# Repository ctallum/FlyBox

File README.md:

# FlyBox - Olin Brandeis Rosbash Lab HMMI FlyBox Redesign SCOPE Project

# About the Firmware
All the source code and documentation for the FlyBox firmware can be found [here](https://github.com/ctallum/FlyBox-firmware)

# About the Web UI
All the source code and documentation for the webside can be found [here](https://github.com/ctallum/FlyBox/tree/main/programming-gui)

## Test Creator Website
To access the website, visit:
https://rosbash-lab-flybox.github.io/FlyBox/

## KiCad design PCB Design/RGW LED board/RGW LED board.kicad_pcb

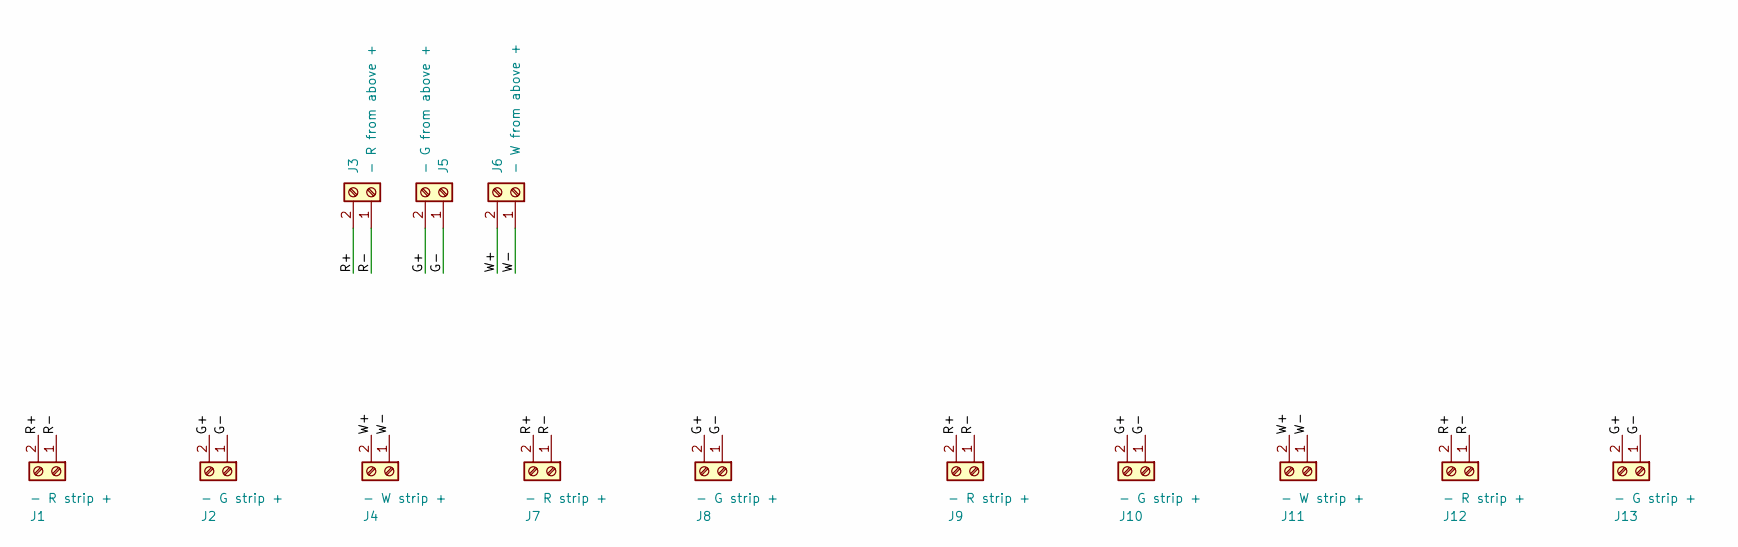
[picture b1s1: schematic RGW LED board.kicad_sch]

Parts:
J1, J7, J9, J12: - R strip +; TerminalBlock_bornier-2_P5.08mm
J2, J8, J10, J13: - G strip +; TerminalBlock_bornier-2_P5.08mm
J3: - R from above +; TerminalBlock_bornier-2_P5.08mm
J4, J11: - W strip +; TerminalBlock_bornier-2_P5.08mm
J5: - G from above +; TerminalBlock_bornier-2_P5.08mm
J6: - W from above +; TerminalBlock_bornier-2_P5.08mm

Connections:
/G+: J2.2, J5.2, J8.2, J10.2, J13.2
/G-: J2.1, J5.1, J8.1, J10.1, J13.1
/R+: J1.2, J3.2, J7.2, J9.2, J12.2
/R-: J1.1, J3.1, J7.1, J9.1, J12.1
/W+: J4.2, J6.2, J11.2
/W-: J4.1, J6.1, J11.1

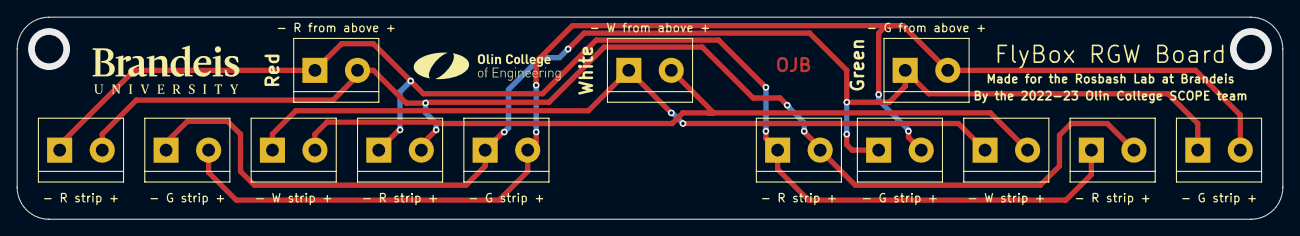
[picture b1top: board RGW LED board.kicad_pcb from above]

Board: 2 copper layers, 151.1 x 24.1 mm, 13 parts (0 on the bottom side), 6 nets.

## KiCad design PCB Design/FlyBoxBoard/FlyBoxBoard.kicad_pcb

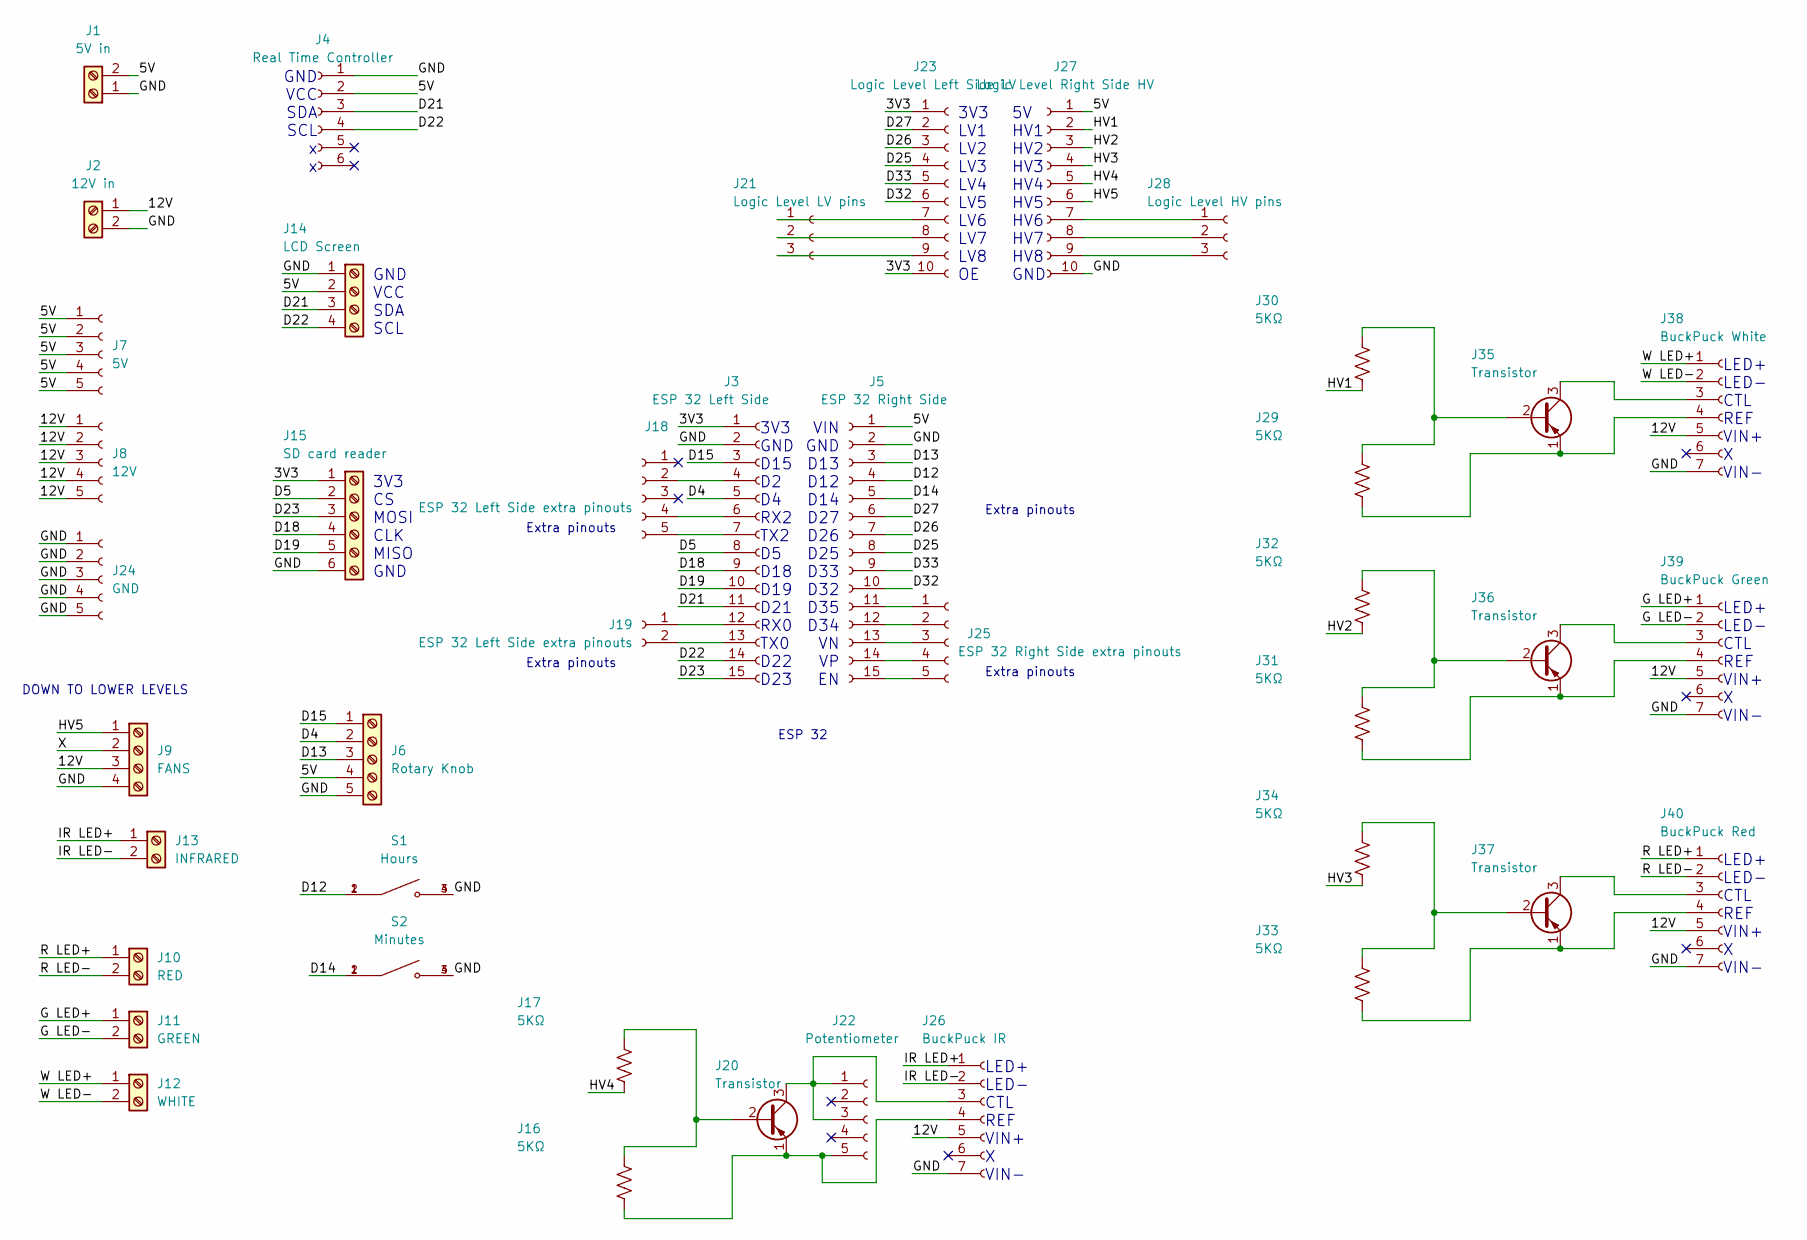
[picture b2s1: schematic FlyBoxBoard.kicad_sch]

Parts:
J1: 5V in; TerminalBlock_bornier-2_P5.08mm
J2: 12V in; TerminalBlock_bornier-2_P5.08mm
J3: ESP 32 Left Side; PinSocket_1x15_P2.54mm_Vertical
J4: Real Time Controller; PinSocket_1x06_P2.54mm_Vertical
J5: ESP 32 Right Side; PinSocket_1x15_P2.54mm_Vertical
J6: Rotary Knob; TerminalBlock_bornier-5_P5.08mm
J7: 5V; PinSocket_1x05_P2.54mm_Vertical
J8: 12V; PinSocket_1x05_P2.54mm_Vertical
J9: FANS; TerminalBlock_bornier-4_P5.08mm
J10: RED; TerminalBlock_bornier-2_P5.08mm
J11: GREEN; TerminalBlock_bornier-2_P5.08mm
J12: WHITE; TerminalBlock_bornier-2_P5.08mm
J13: INFRARED; TerminalBlock_bornier-2_P5.08mm
J14: LCD Screen; TerminalBlock_bornier-4_P5.08mm
J15: SD card reader; TerminalBlock_bornier-6_P5.08mm
J16, J17, J29, J30, J31, J32, J33, J34: 5KΩ; R_0805_2012Metric_Pad1.20x1.40mm_HandSolder
J18: ESP 32 Left Side extra pinouts; PinSocket_1x05_P2.54mm_Vertical
J19: ESP 32 Left Side extra pinouts; PinSocket_1x02_P2.54mm_Vertical
J20, J35, J36, J37: Transistor; TO-92_Inline
J21: Logic Level LV pins; PinSocket_1x03_P2.54mm_Vertical
J22: Potentiometer; PinSocket_1x05_P2.54mm_Vertical
J23: Logic Level Left Side LV; PinSocket_1x10_P2.54mm_Vertical
J24: GND; PinSocket_1x05_P2.54mm_Vertical
J25: ESP 32 Right Side extra pinouts; PinSocket_1x05_P2.54mm_Vertical
J26: BuckPuck IR; PinSocket_1x07_P2.54mm_Vertical
J27: Logic Level Right Side HV; PinSocket_1x10_P2.54mm_Vertical
J28: Logic Level HV pins; PinSocket_1x03_P2.54mm_Vertical
J38: BuckPuck White; PinSocket_1x07_P2.54mm_Vertical
J39: BuckPuck Green; PinSocket_1x07_P2.54mm_Vertical
J40: BuckPuck Red; PinSocket_1x07_P2.54mm_Vertical
S1: Hours; SW_1571563-2; PARTREV V
S2: Minutes; SW_1571563-2; PARTREV V

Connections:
/3V3: J3.1, J15.1, J23.1, J23.10
/5V: J1.2, J4.2, J5.1, J6.4, J7.1, J7.2, J7.3, J7.4, J7.5, J14.2, J27.1
/12V: J2.1, J8.1, J8.2, J8.3, J8.4, J8.5, J9.3, J26.5, J38.5, J39.5, J40.5
/D4: J3.5, J6.2
/D5: J3.8, J15.2
/D12: J5.4, S1.1, S1.2
/D13: J5.3, J6.3
/D14: J5.5, S2.1, S2.2
/D15: J3.3, J6.1
/D18: J3.9, J15.4
/D19: J3.10, J15.5
/D21: J3.11, J4.3, J14.3
/D22: J3.14, J4.4, J14.4
/D23: J3.15, J15.3
/D25: J5.8, J23.4
/D26: J5.7, J23.3
/D27: J5.6, J23.2
/D32: J5.10, J23.6
/D33: J5.9, J23.5
/G LED+: J11.1, J39.1
/G LED-: J11.2, J39.2
/GND: J1.1, J2.2, J3.2, J4.1, J5.2, J6.5, J9.4, J14.1, J15.6, J24.1, J24.2, J24.3, J24.4, J24.5, J26.7, J27.10, J38.7, J39.7, J40.7, S1.3, S1.4, S2.3, S2.4
/HV1: J27.2, J30.2
/HV2: J27.3, J32.2
/HV3: J27.4, J34.2
/HV4: J17.2, J27.5
/HV5: J9.1, J27.6
/IR LED+: J13.1, J26.1
/IR LED-: J13.2, J26.2
/R LED+: J10.1, J40.1
/R LED-: J10.2, J40.2
/W LED+: J12.1, J38.1
/W LED-: J12.2, J38.2
/X: J9.2
unnamed: J16.1, J17.1, J20.2 (B)
unnamed 35: J16.2, J20.1 (E), J22.5, J26.4; also elsewhere on the board
unnamed: J3.4, J18.2
unnamed: J3.6, J18.4
unnamed: J3.7, J18.5
unnamed: J3.12, J19.1
unnamed: J3.13, J19.2
unnamed 41: J20.3 (C), J22.1, J22.3, J26.3; also elsewhere on the board
unnamed: J21.1, J23.7
unnamed: J21.2, J23.8
unnamed: J21.3, J23.9
unnamed: J5.11, J25.1
unnamed: J5.12, J25.2
unnamed: J5.13, J25.3
unnamed: J5.14, J25.4
unnamed: J5.15, J25.5
unnamed: J27.7, J28.1
unnamed: J27.8, J28.2
unnamed: J27.9, J28.3
unnamed: J29.1, J30.1, J35.2 (B)
unnamed: J29.2, J35.1 (E), J38.4
unnamed: J31.1, J32.1, J36.2 (B)
unnamed: J31.2, J36.1 (E), J39.4
unnamed: J33.1, J34.1, J37.2 (B)
unnamed: J33.2, J37.1 (E), J40.4
unnamed: J35.3 (C), J38.3
unnamed: J36.3 (C), J39.3
unnamed: J37.3 (C), J40.3

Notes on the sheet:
3V3 CS MOSI CLK MISO GND
DOWN TO LOWER LEVELS
VIN GND D13 D12 D14 D27 D26 D25 D33 D32 D35 D34 VN VP EN
GND VCC SDA SCL
3V3 LV1 LV2 LV3 LV4 LV5 LV6 LV7 LV8 OE
5V HV1 HV2 HV3 HV4 HV5 HV6 HV7 HV8 GND
ESP 32
3V3 GND D15 D2 D4 RX2 TX2 D5 D18 D19 D21 RX0 TX0 D22 D23
Extra pinouts
LED+ LED- CTL REF VIN+ X VIN-
GND VCC SDA SCL x x

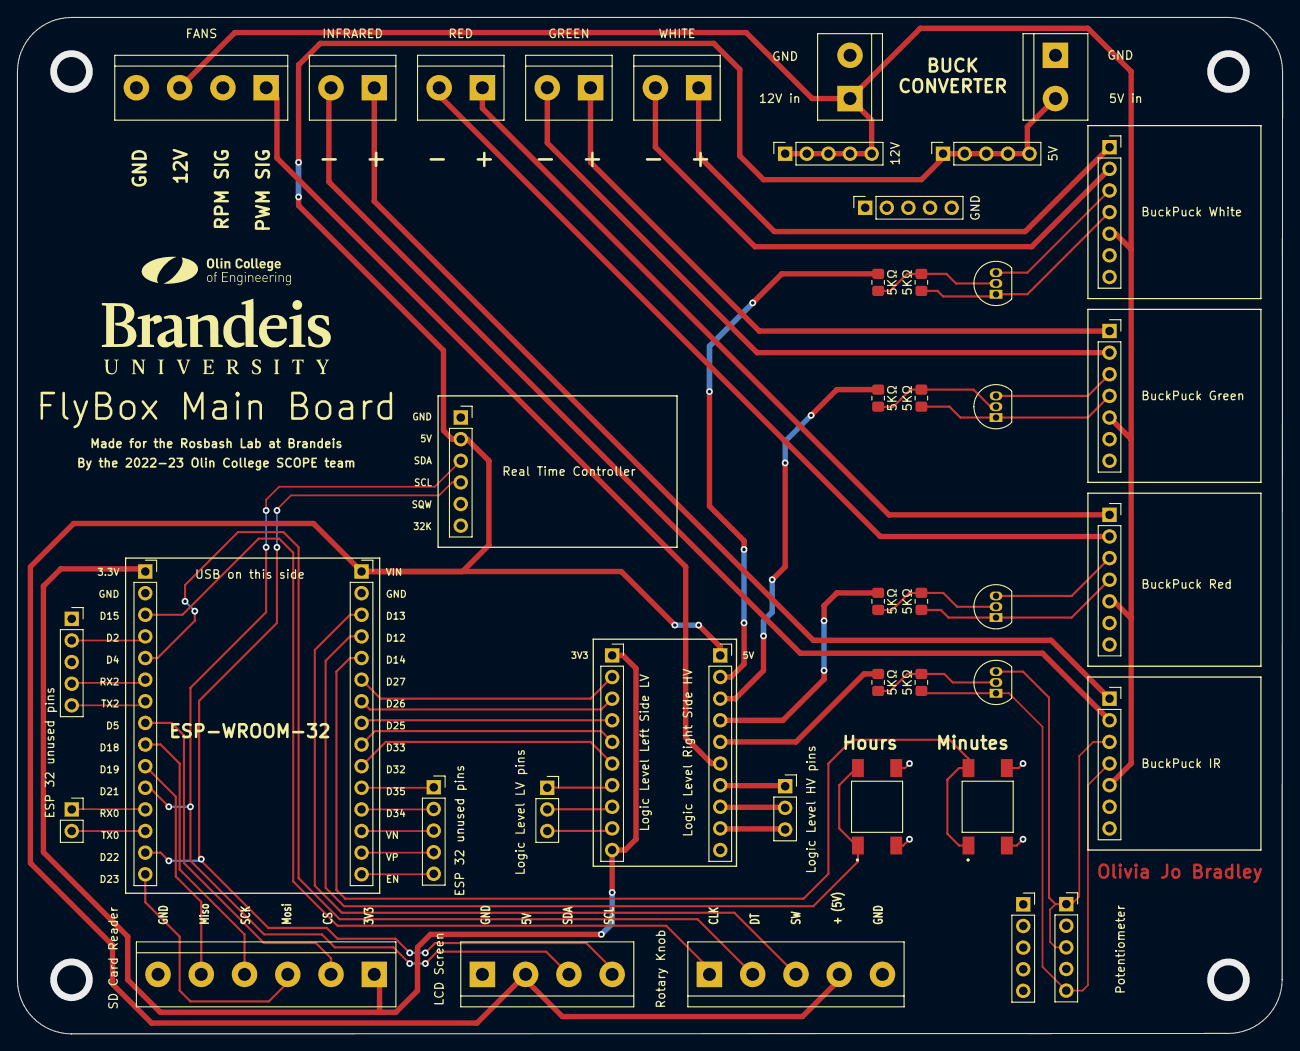
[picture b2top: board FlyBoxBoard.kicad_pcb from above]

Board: 2 copper layers, 148.6 x 119.4 mm, 43 parts (0 on the bottom side), 61 nets.

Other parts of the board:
J22#2: Potentiometer; PinSocket_1x05_P2.54mm_Vertical

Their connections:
unnamed 35: J22#2.5; also elsewhere on the board
unnamed 41: J22#2.1, J22#2.3; also elsewhere on the board

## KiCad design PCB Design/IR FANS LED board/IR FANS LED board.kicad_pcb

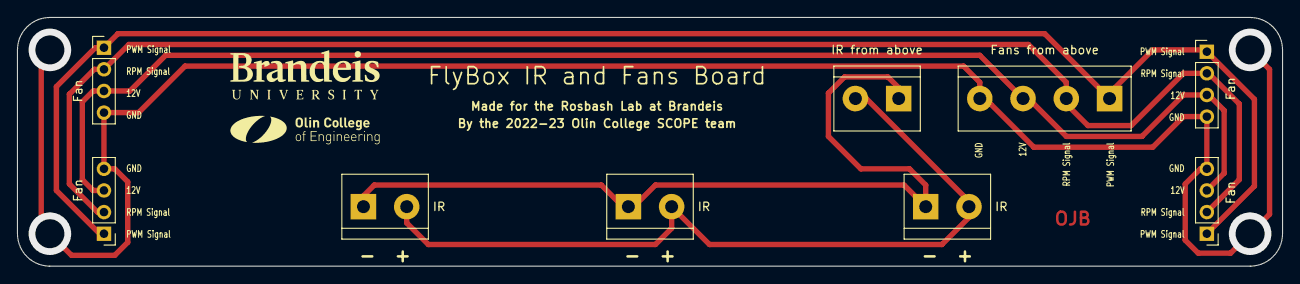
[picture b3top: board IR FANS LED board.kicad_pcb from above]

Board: 2 copper layers, 148.6 x 29.2 mm, 9 parts (0 on the bottom side), 6 nets.

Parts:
J1, J2, J8, J9: Fan; PinHeader_1x04_P2.54mm_Vertical
J3, J5, J7: IR; TerminalBlock_bornier-2_P5.08mm
J4: Fans from above; TerminalBlock_bornier-4_P5.08mm
J6: IR from above; TerminalBlock_bornier-2_P5.08mm

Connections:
/12V: J1.3, J2.3, J4.3, J8.3, J9.3
/GND: J1.4, J2.4, J4.4, J8.4, J9.4
/HV5: J1.1, J2.1, J4.1, J8.1, J9.1
/IR LED+: J3.2, J5.2, J6.2, J7.2
/IR LED-: J3.1, J5.1, J6.1, J7.1
/X: J1.2, J2.2, J4.2, J8.2, J9.2

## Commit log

2022-10-12 Add sample flybox Arduino code
2022-10-12 Add test copy of RedLED example code to experiment with
2022-11-16 V1
    Front end mostly done, back end not started
2022-11-16 Add Arduino code and profile.json
2022-11-16 clean up repo
2022-11-16 Fix typo in profile.txt file
2022-11-17 Download working
    Downloading items sort of works, but uses a new button that's not in the header. I'm going to try to fix this in further versions.
2022-11-17 Download fully working
    Download button is now in the right spot. Refresh button works but upload does not.
2022-11-30 Uploading LED test code + Temp sensor
2022-12-01 Item colors working properly
    About to try implementing upload button, but things are working for the moment.
2022-12-07 Upload button working
    Upload button works, item drag precision increased to one minute, clicking on timeline creates new event.
2022-12-07 Update firmware to deserialize by chunk and create file selection menu
2022-12-09 Updated with ESP Pins
    #define WHITEPIN 26
    #define REDPIN 25
    #define GREENPIN 27
    #define IRPIN 33
2022-12-12 get working!
2022-12-12 rename files
2022-12-12 Fix bottons on box
2022-12-14 Add check for end of test
2022-12-14 move files around
2023-01-26 actual base component
2023-01-26 remove duplicate files
2023-01-26 use components as components
2023-01-27 typescript
2023-01-27 function components
2023-01-28 move state management up to app
2023-01-28 reorganize and clean up timeline code
2023-01-28 misc clean up
2023-01-30 add day button
2023-01-30 add hours on top, formatting
2023-01-31 remove day logic
2023-01-31 remove day button
2023-01-31 move without click
2023-01-31 fix id conflict bug
2023-01-31 move day buttons
2023-02-01 export as day hour min
2023-02-03 export format changes
2023-02-03 gh pages setup
2023-02-03 upload new file format
2023-02-04 basic event handling
2023-02-07 intensity slider
2023-02-07 frequency slider
2023-02-07 make the app not crash catastrophically
2023-02-08 prevent crossing day lines
2023-02-08 sunset mode
2023-02-08 start of time stuff
2023-02-08 homepage setting
2023-02-08 update firmware for new timings
2023-02-08 2/8 PCB schematics
2023-02-09 schematic now has no errors
2023-02-09 Labeling on components
2023-02-09 timepicker saves time
2023-02-10 Layout progress
2023-02-10 open context menu on click
2023-02-10 PCB progress
2023-02-10 Main PCB complete
2023-02-11 add types
2023-02-11 help modal structure
2023-02-12 start of overlap logic
2023-02-12 quick type fix
2023-02-12 refactor time conversions
2023-02-12 oops also update that
2023-02-12 show time on event
2023-02-12 hover colors
2023-02-12 time formatting
2023-02-13 oops
2023-02-13 reset confirm modal
2023-02-13 remove modal border
2023-02-13 fix resize validator
2023-02-13 on create, snap to hour
2023-02-13 custom cursor
2023-02-13 Finished IR and RGW board
2023-02-15 show correct num days when uploading
2023-02-15 actually save context menu data
2023-02-15 close context menu on esc
2023-02-15 add button margin
2023-02-15 no up button on top day
2023-02-15 Zachary FlyBoxBoard review and edits
2023-02-15 Ordering Fixes
2023-02-15 Zachary IR and RGW LED boards revisions
2023-02-17 snap to 15 min
2023-02-17 add day when move last day down
2023-02-17 dont open menu on right click
2023-02-17 close modal button
2023-02-17 make context menu not go offscreen
2023-02-17 handle overlap
2023-02-18 quick fix
2023-02-18 summary info
2023-02-18 sliders to text input
2023-02-18 css clean up and organize
2023-02-18 Backups?
2023-02-20 sunset mode help button
2023-02-20 save on enter
2023-02-20 undo redo with keyboard shortcuts
2023-02-22 update for new time JSON and UI refresh
2023-02-22 Gerber Files
2023-02-22 Logos and labels
2023-02-22 Removing old drill files
2023-02-23 Backups
2023-02-25 ctrl c ctrl v copy paste selected events
2023-02-25 right click paste on specific day
2023-02-25 copy paste bug fixes
2023-02-25 change default days to 1
2023-02-25 don't delete last day
2023-02-25 swap upload/download order
2023-02-26 font and favicon
2023-02-26 button style changes
2023-02-26 day left side css
2023-02-26 drop shadows
2023-02-28 drag and drop logic
2023-02-28 drag and drop fixes
2023-02-28 css fixes
2023-02-28 upload button fix
2023-02-28 dont crash app on empty upload
2023-03-01 Updated mounting holes and rounded corneres
2023-03-01 3/1 updates
2023-03-01 refactor firmware
2023-03-01 3/1 Changes pt 2
2023-03-01 get rotary knob working
2023-03-02 ctrl a, ctrl y
2023-03-02 drop zone style
2023-03-02 sidebar remove bottom border
2023-03-02 remove sunset mode ? button
2023-03-02 tooltips
2023-03-02 new header buttons
2023-03-02 context menu handle switching events
2023-03-02 default frequency 0
2023-03-04 download specify name
2023-03-04 cmd key
2023-03-04 safari is stupid
2023-03-04 aaaaa
2023-03-07 custom version of rct as submodule
2023-03-07 Adjust event handling
2023-03-07 fix SD card response if none detected
2023-03-07 update time reads
2023-03-07 intro screne and rtc time adjust
2023-03-07 refactor into folders
2023-03-07 refactor status screen
2023-03-07 update SD card error hadnling
2023-03-07 context menu styles
2023-03-07 add day margin
2023-03-08 fix broken read if 3 files
2023-03-08 implement global reset and change update and finish screens
2023-03-08 tweaks
2023-03-08 clean up lcd global calls
2023-03-08 update add hour/min function calls
2023-03-08 clean up rtc function calls
2023-03-08 update func names
2023-03-08 modify how pin status is handled and also fix percent indicator
2023-03-08 3/8 Work
    Missing button footprint
2023-03-08 drag to create event
2023-03-08 download modal fixes
2023-03-08 drag to top
2023-03-09 V2 IR and RGW boards done
    Main board missing button footprint
2023-03-09 Finished V2 PCBs with rounded edges
2023-03-09 Zachary first pass on V2 of FlyBoxBoard
    Not done yet, still need to look at/think about more.
2023-03-09 Shrunk vias, fixed ohms and XV1 labels
2023-03-11 Zachary second pass on FlyBoxBoard
    Pretty much ready to go after OJ checks again and reviews my notes in Teams.
    I still have not checked the other two boards.
2023-03-12 Zachary review of IR and RGW and Fans boards
    @oliviajobradley All done reviewing all three boards. I played with the silkscreen a bit, not sure if it's better or worse. OJ, feel free to change it back if you'd prefer.
    Let's order!
2023-03-12 A few more PCB edits
    - Eliminated and/or shortened traces on rear side (no more long traces on the rear side)
    - Connected four screw vias on IR board to GND
    - Ran DRC on all boards and addressed issues where necessary
    Imo, we should be ready to order on @oliviajobradley's approval.
2023-03-19 copy day right click menu
2023-03-19 big refactor
2023-03-20 misc code fixes
2023-03-20 paste button
2023-03-21 drag drop style
2023-03-22 misc
2023-03-22 fixes
2023-03-22 remove old code
2023-03-22 Version 3 Assembly Edits
2023-03-22 Update react-calendar-timeline
2023-03-22 Fixed capitalization
2023-03-22 Zachary final review of PCBs
2023-03-22 add docstrings
2023-03-22 Adding board BOMs
2023-03-22 show current time in status screen
2023-03-23 fix time being weird
2023-03-23 remove sunset mode
2023-03-24 drag and drop cursor image
2023-03-27 allow backwards drag when creating events
2023-03-27 show drag to create
2023-03-27 fix font
2023-03-27 change to number input
2023-03-28 V3 Gerbers and STEP Files
2023-03-29 move firmware to submodule
2023-03-29 Centroid file
2023-03-29 update submodules again ...
2023-03-29 set up submodules again using ssh
2023-03-29 lets try this agian
2023-03-29 add firmware submodule
2023-03-31 help modal content
2023-03-31 rct submodule update
2023-04-02 add olin logo to modal
2023-04-02 fix drag to top issues
2023-04-02 fix x button
2023-04-04 electron setup
2023-04-04 move icon
2023-04-05 rct fix
2023-04-05 fix drag to create bugs
2023-04-05 context menu x to close without saving
2023-04-05 clickaway bugs
2023-04-10 idk what im doing
2023-04-10 small fixes
2023-04-11 validate time inputs better
2023-04-12 drag to create both directions
2023-04-18 unselect
2023-04-18 overlap check prevent negative time
2023-04-19 add fabrication directory
2023-04-21 readme
2023-04-22 context menu bugs, add help link
2023-04-22 copy individual items
2023-05-03 Added 3D print files
2023-05-03 Remove firmware submodule
2023-05-03 Add back firmware submodule
2023-05-03 add photos
2023-05-03 remove photos bc it wasn't needed
2023-05-03 Lasercut Files
2023-05-03 PCB Zip files
2023-05-03 Uploading V2 of BOM and Instructions
2023-05-07 Version 3
